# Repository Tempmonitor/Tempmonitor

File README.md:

#Temp monitor
Temp monitor is a device the monitors system resources. It connects to a computer with a micro usb cable and a host program written in C# collects and sends system information to the device. 

The device is equiped with four 3 character 8-segments led displays. The device is controlled by a ATiny45 running the V-USB library to create create a HID USB device. 

More information about hardware, firmware and host softwar can be found in the subfolders of the repository.

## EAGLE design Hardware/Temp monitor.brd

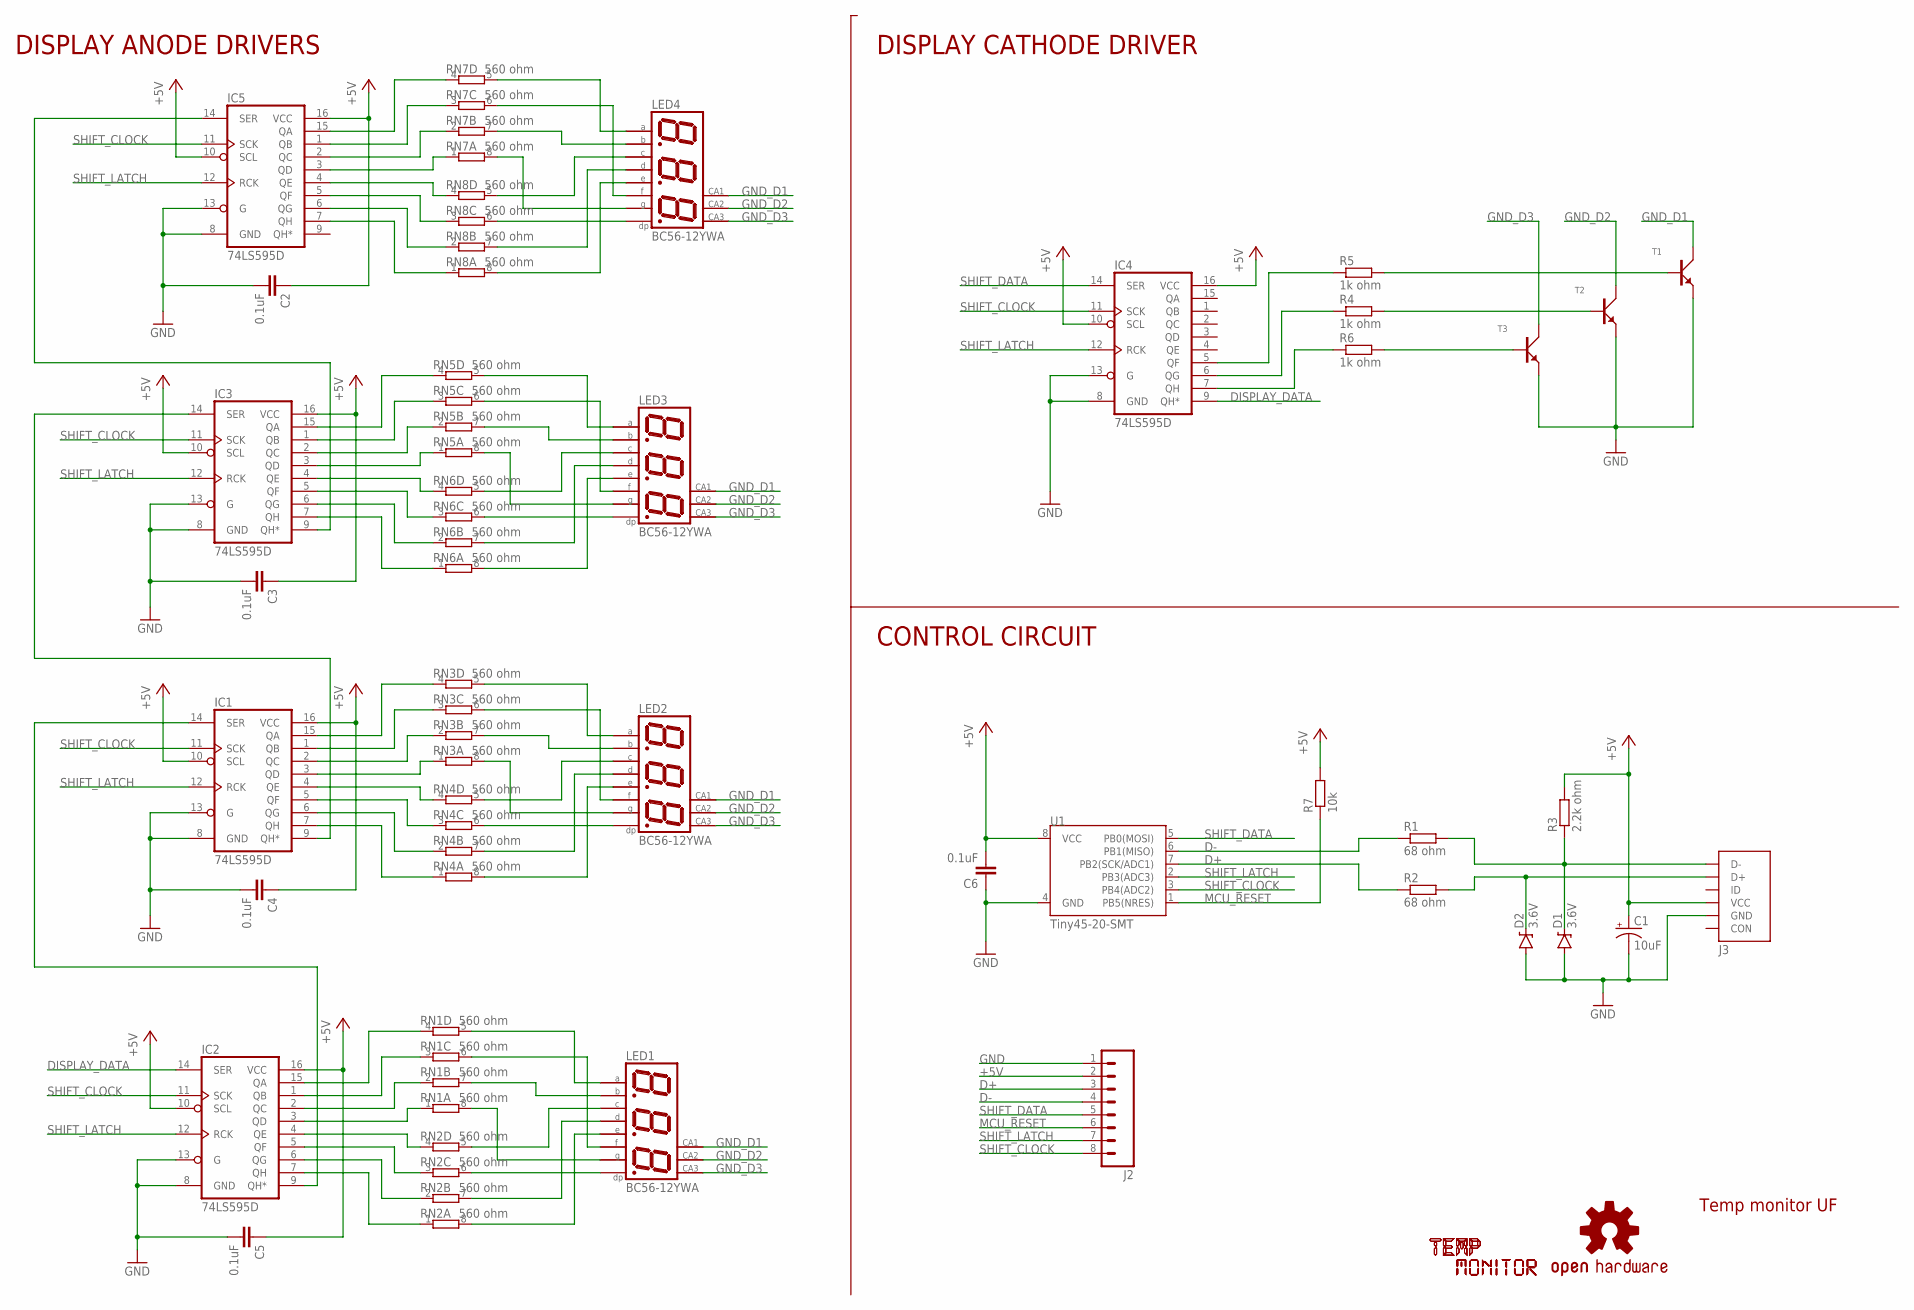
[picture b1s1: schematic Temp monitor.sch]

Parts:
C1: 10uF; NIPPON_F80
C2, C3, C4, C5, C6: 0.1uF; C0805
D1, D2: 3.6V; SOD-123
IC1, IC2, IC3, IC4, IC5: 74LS595D; SO16
J2: TP_8
J3: ZX62D-B-5PA8
LED1, LED2, LED3, LED4: BC56-12YWA; BX56-12
LOGO1: OSHW-LOGOL; OSHW-LOGO-L
R1, R2: 68 ohm; R0805W
R3: 2.2k ohm; R0805W
R4, R5, R6: 1k ohm; R0805W
R7: 10k; R0805W
RN1, RN2, RN3, RN4, RN5, RN6, RN7, RN8: 560 ohm; EXBV8V
T1, T2, T3: NPN; SOT23
U1: Tiny45-20-SMT; SO08-EIAJ
U$1, U$2: LOGO; LOGO_M

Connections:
+5V: C1.+, C2.1, C3.1, C4.1, C5.1, C6.2, IC1.10 (SCL), IC1.16 (VCC), IC2.10 (SCL), IC2.16 (VCC), IC3.10 (SCL), IC3.16 (VCC), IC4.10 (SCL), IC4.16 (VCC), IC5.10 (SCL), IC5.16 (VCC), J2.2, J3.VCC, R3.2, R7.2, U1.8 (VCC)
D+: J2.3, R2.1, U1.7 (PB2(SCK/ADC1))
D-: J2.4, R1.1, U1.6 (PB1(MISO))
DISPLAY_DATA: IC2.14 (SER), IC4.9 (QH*)
GND: C1.-, C2.2, C3.2, C4.2, C5.2, C6.1, D1.A, D2.A, IC1.8 (GND), IC1.13 (G), IC2.8 (GND), IC2.13 (G), IC3.8 (GND), IC3.13 (G), IC4.8 (GND), IC4.13 (G), IC5.8 (GND), IC5.13 (G), J2.1, J3.GND, T1.2 (E), T2.2 (E), T3.2 (E), U1.4 (GND)
GND_D1: LED1.12 (CA), LED2.12 (CA), LED3.12 (CA), LED4.12 (CA), T1.3 (C)
GND_D2: LED1.9 (CA), LED2.9 (CA), LED3.9 (CA), LED4.9 (CA), T2.3 (C)
GND_D3: LED1.8 (CA), LED2.8 (CA), LED3.8 (CA), LED4.8 (CA), T3.3 (C)
MCU_RESET: J2.6, R7.1, U1.1 (PB5(NRES))
unnamed: D1.C, J3.D-, R1.2, R3.1
unnamed: D2.C, J3.D+, R2.2
unnamed: IC2.15 (QA), RN1.4 (1)
unnamed: IC2.1 (QB), RN1.3 (1)
unnamed: IC4.7 (QH), R6.1
unnamed: IC2.2 (QC), RN1.2 (1)
unnamed: IC2.3 (QD), RN1.1
unnamed: IC2.4 (QE), RN2.4 (1)
unnamed: IC2.5 (QF), RN2.3 (1)
unnamed: IC2.6 (QG), RN2.2 (1)
unnamed: IC2.7 (QH), RN2.1
unnamed: LED1.4 (C), RN2.5 (2)
unnamed: LED1.7 (B), RN1.7 (2)
unnamed: LED1.11 (A), RN1.5 (2)
unnamed: LED1.10 (F), RN1.6 (2)
unnamed: LED1.5 (G), RN1.8 (2)
unnamed: LED1.2 (D), RN2.7 (2)
unnamed: LED1.3 (DP), RN2.6 (2)
unnamed: LED1.1 (E), RN2.8 (2)
unnamed: IC1.15 (QA), RN3.4 (1)
unnamed: IC1.1 (QB), RN3.3 (1)
unnamed: IC1.2 (QC), RN3.2 (1)
unnamed: IC1.3 (QD), RN3.1
unnamed: IC1.4 (QE), RN4.4 (1)
unnamed: IC1.5 (QF), RN4.3 (1)
unnamed: IC1.6 (QG), RN4.2 (1)
unnamed: IC1.7 (QH), RN4.1
unnamed: LED2.1 (E), RN4.8 (2)
unnamed: LED2.2 (D), RN4.7 (2)
unnamed: LED2.4 (C), RN4.5 (2)
unnamed: IC4.6 (QG), R4.1
unnamed: IC4.5 (QF), R5.1
unnamed: IC5.15 (QA), RN7.4 (1)
unnamed: R4.2, T2.1 (B)
unnamed: R5.2, T1.1 (B)
unnamed: R6.2, T3.1 (B)
unnamed: LED2.7 (B), RN3.7 (2)
unnamed: LED2.11 (A), RN3.5 (2)
unnamed: LED2.10 (F), RN3.6 (2)
unnamed: LED2.5 (G), RN3.8 (2)
unnamed: LED2.3 (DP), RN4.6 (2)
unnamed: IC3.15 (QA), RN5.4 (1)
unnamed: IC3.1 (QB), RN5.3 (1)
unnamed: IC3.2 (QC), RN5.2 (1)
unnamed: IC3.3 (QD), RN5.1
unnamed: IC3.4 (QE), RN6.4 (1)
unnamed: IC3.5 (QF), RN6.3 (1)
unnamed: IC3.6 (QG), RN6.2 (1)
unnamed: IC3.7 (QH), RN6.1
unnamed: LED3.1 (E), RN6.8 (2)
unnamed: LED3.2 (D), RN6.7 (2)
unnamed: LED3.4 (C), RN6.5 (2)
unnamed: LED3.7 (B), RN5.7 (2)
unnamed: LED3.11 (A), RN5.5 (2)
unnamed: LED3.10 (F), RN5.6 (2)
unnamed: LED3.5 (G), RN5.8 (2)
unnamed: LED3.3 (DP), RN6.6 (2)
unnamed: IC5.1 (QB), RN7.3 (1)
unnamed: IC5.2 (QC), RN7.2 (1)
unnamed: IC5.3 (QD), RN7.1
unnamed: IC5.4 (QE), RN8.4 (1)
unnamed: IC5.5 (QF), RN8.3 (1)
unnamed: IC5.6 (QG), RN8.2 (1)
unnamed: IC5.7 (QH), RN8.1
unnamed: LED4.1 (E), RN8.8 (2)
unnamed: LED4.2 (D), RN8.7 (2)
unnamed: LED4.4 (C), RN8.5 (2)
unnamed: LED4.7 (B), RN7.7 (2)
unnamed: LED4.11 (A), RN7.5 (2)
unnamed: LED4.10 (F), RN7.6 (2)
unnamed: LED4.5 (G), RN7.8 (2)
unnamed: LED4.3 (DP), RN8.6 (2)
unnamed: IC3.9 (QH*), IC5.14 (SER)
unnamed: IC1.9 (QH*), IC3.14 (SER)
unnamed: IC1.14 (SER), IC2.9 (QH*)
SHIFT_CLOCK: IC1.11 (SCK), IC2.11 (SCK), IC3.11 (SCK), IC4.11 (SCK), IC5.11 (SCK), J2.8, U1.3 (PB4(ADC2))
SHIFT_DATA: IC4.14 (SER), J2.5, U1.5 (PB0(MOSI))
SHIFT_LATCH: IC1.12 (RCK), IC2.12 (RCK), IC3.12 (RCK), IC4.12 (RCK), IC5.12 (RCK), J2.7, U1.2 (PB3(ADC3))

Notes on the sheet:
DISPLAY CATHODE DRIVER
DISPLAY ANODE DRIVERS
Temp monitor UF
CONTROL CIRCUIT

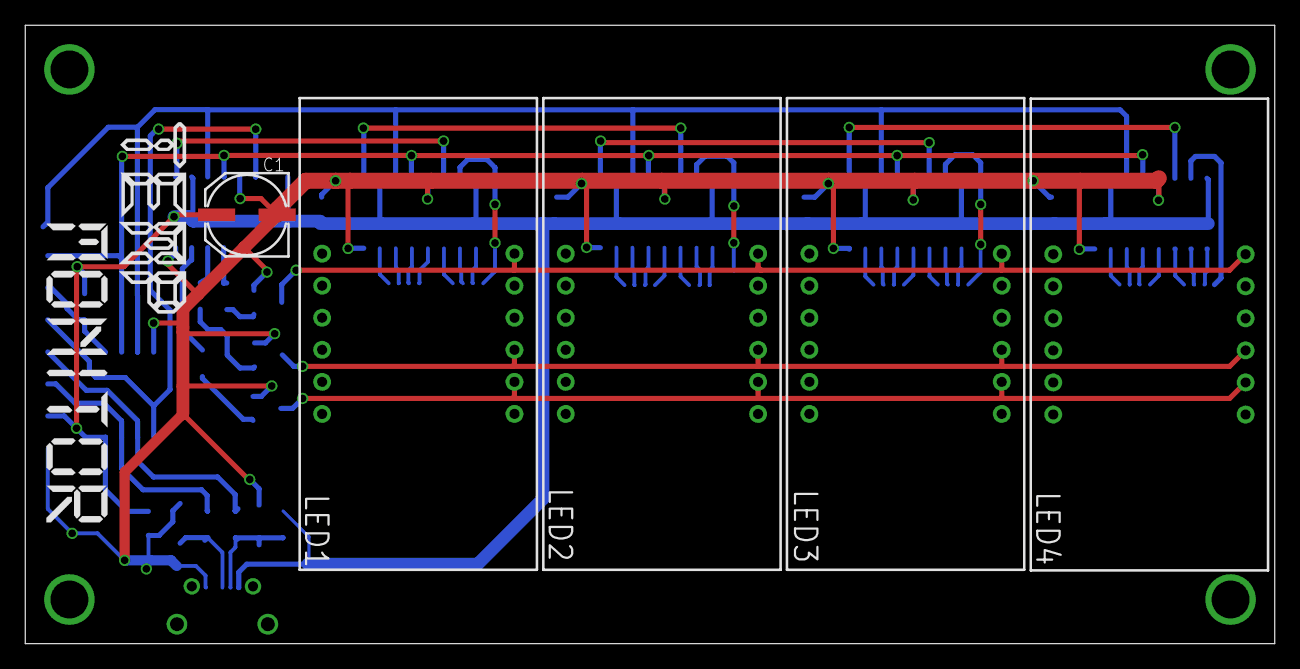
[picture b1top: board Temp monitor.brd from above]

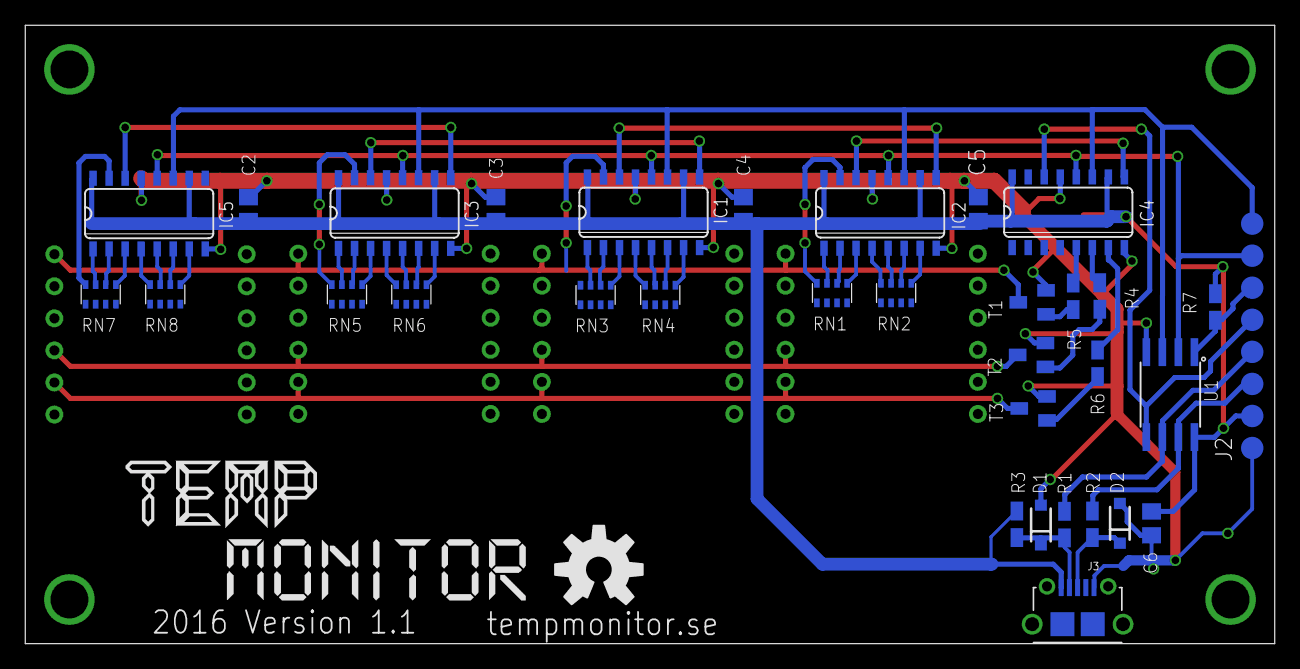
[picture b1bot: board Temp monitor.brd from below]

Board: 2 copper layers, 99.0 x 49.0 mm, 41 parts (35 on the bottom side), 87 nets.

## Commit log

2016-09-06 Initial hardware
    PCBnew not complete.
2016-09-17 Basic interface (Dummy)
2016-09-17 Design + added ballonTip
2016-09-18 Writes and loads user settings
2016-09-18 Removed unused array
2016-09-18 Added inno setup
2016-09-18 32-bit compile
2016-09-18 Fix elevated user promt
2016-09-18 Added library and licenses
2016-09-22 Update
    Gerber files added, BOM added, PCB redone, separate clock traces for
    led-drivers made.
2016-09-23 Update
    Logo exchanged, gerbers updated and BOM updated and redone, now with MPN
    instead of Seeed SKU.
2016-09-23 Hotfix
    Values not included in gerber.
2016-10-05 Added inital new pcb version
2016-10-06 Firmware base framework
2016-10-19 PCB layout
    PCB routed, need of silkscreen fixes. Directory clean up.
2016-10-20 Added loggos
2016-10-23 USB circuit fix
    USB circuit fix R3 incorrectly connected. Added filtering capacitors to MCU and shift registers. Centered displays.
2016-10-23 Fix LED display wiring
2016-10-25 PCB fix
    Removed C6 value+ more space for R3, R1 & D1
2016-10-27 Hotfix
    Unnecessary front silkscreen removed, some silkscreen moved from front
    to back and silkscreen references moved.
2016-11-23 Version 1.0
2016-11-23 Gerber files Version 1.0
2016-11-23 Fix corrupted file
2016-12-15 Update Added codeblocks project, license-, display- and shift register files.
2016-12-15 removed binaries
2016-12-15 Added resource directory
2016-12-15 Fixed typo
2016-12-15 Updated files in project
2016-12-18 Added HidLibrary
2016-12-18 License update
2016-12-19 Moved files
2016-12-19 Added host files
2016-12-19 Added main licens and readme
2016-12-19 Added schematic in PDF
2016-12-20 Typo
2016-12-22 Revert "Hotfix"
    This reverts commit b01ab2ca72f5422068492f297ba1483d4015dfa4.
2016-12-23 Various updates Automatic oscillator calibration, display driver
2017-01-07 Comments added and timer routine cleanup
2017-01-08 Cleanup
2017-01-09 Faster shiftout Increased transfer speed
2017-01-09 Device connection made and label change added
2017-01-09 HID reconnection added
2017-01-10 Minor cleanup
2017-01-10 Test output and slider added
2017-01-10 USB Config update Updated VID, PID, vendor name and device name
2017-01-10 Updated display function Remove 0 before number
2017-01-11 Outputdata function started
2017-01-11 Changed icons
2017-01-11 Compiled test installationfile
2017-01-11 Output and UI value working
2017-01-11 Minor fix
    Changed Display 2 Combobox to correct style.
2017-01-11 Return GPU load and temperature fix
2017-01-12 Changed VID & PID, added battery info
2017-01-14 Autostart
2017-01-14 Added license
2017-01-14 Esthetical fix
2017-01-14 Autorun as default, only show form first time
2017-01-14 Notifyicon shows status
2017-01-14 Changed assemblyname and removed notfication ballones
2017-02-02 Receive raw data from computer Instead of receiving digit numbers computer controls all the display segments
2017-02-02 Brightness control Using Timer1 compare match to control brightness of displays.
2017-02-02 Remove test project
2017-02-02 Removed unused controles
2017-02-18 Receive plain data, turn of display on low brightness
2017-02-18 Added brightness control
2017-02-19 Compiled installation file
2017-02-25 USB recive timout If no data have been received in a cirtain amount of time, turn of displays.
2017-02-26 Cleanup + through hole usb
2017-03-02 Moved shift registers Board is not completed

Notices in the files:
parts and their libraries:
SparkFun-DiscreteSemi: Licensing: Creative Commons ShareAlike 4.0 International - https://creativecommons.org/licenses/by-sa/4.0
